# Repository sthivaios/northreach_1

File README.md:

# NorthReach 1

## Introduction

NorthReach 1 is a wired USB remote controller, to aid during presentations, particularly
on touchscreen interactive whiteboards.

Apart from basic features that other commercially available presenter remotes have, NorthReach
includes buttons for controlling Windows computers by default, such as a separate button for closing
the focused window, or a button to bring up Task Manager in the event that some application freezes.

The firmware is written in C, with the Espressif ESP-IDF framework. Through the `menuconfig` utility,
the board can be reconfigured to assign different actions to any button, for example to make the remote
compatible with MacOS.

Additionally, under the `hardware/` directory, the KiCad project for the PCB is available, as well
as the 3D printed enclosure inside `enclosure/`.

**The firmware and the PCB is only designed for ESP-S3 modules which natively support USB.**

In the future, there will also be a wireless version of NorthReach, possibly based on a Nordic nRF SoC.
However, for now, I'm focusing on the wired version.

## Contributing

You are more than welcome to contribute to the project, by forking then creating a pull request.
If you are an end user, feel free to request new features or report a bug by creating an issue
on this repository on GitHub.

If you are actually contributing code to the project, make sure that you understand the license terms.

## Licensing
This project contains multiple components under different licenses.
See [LICENSE](LICENSE) for more details.

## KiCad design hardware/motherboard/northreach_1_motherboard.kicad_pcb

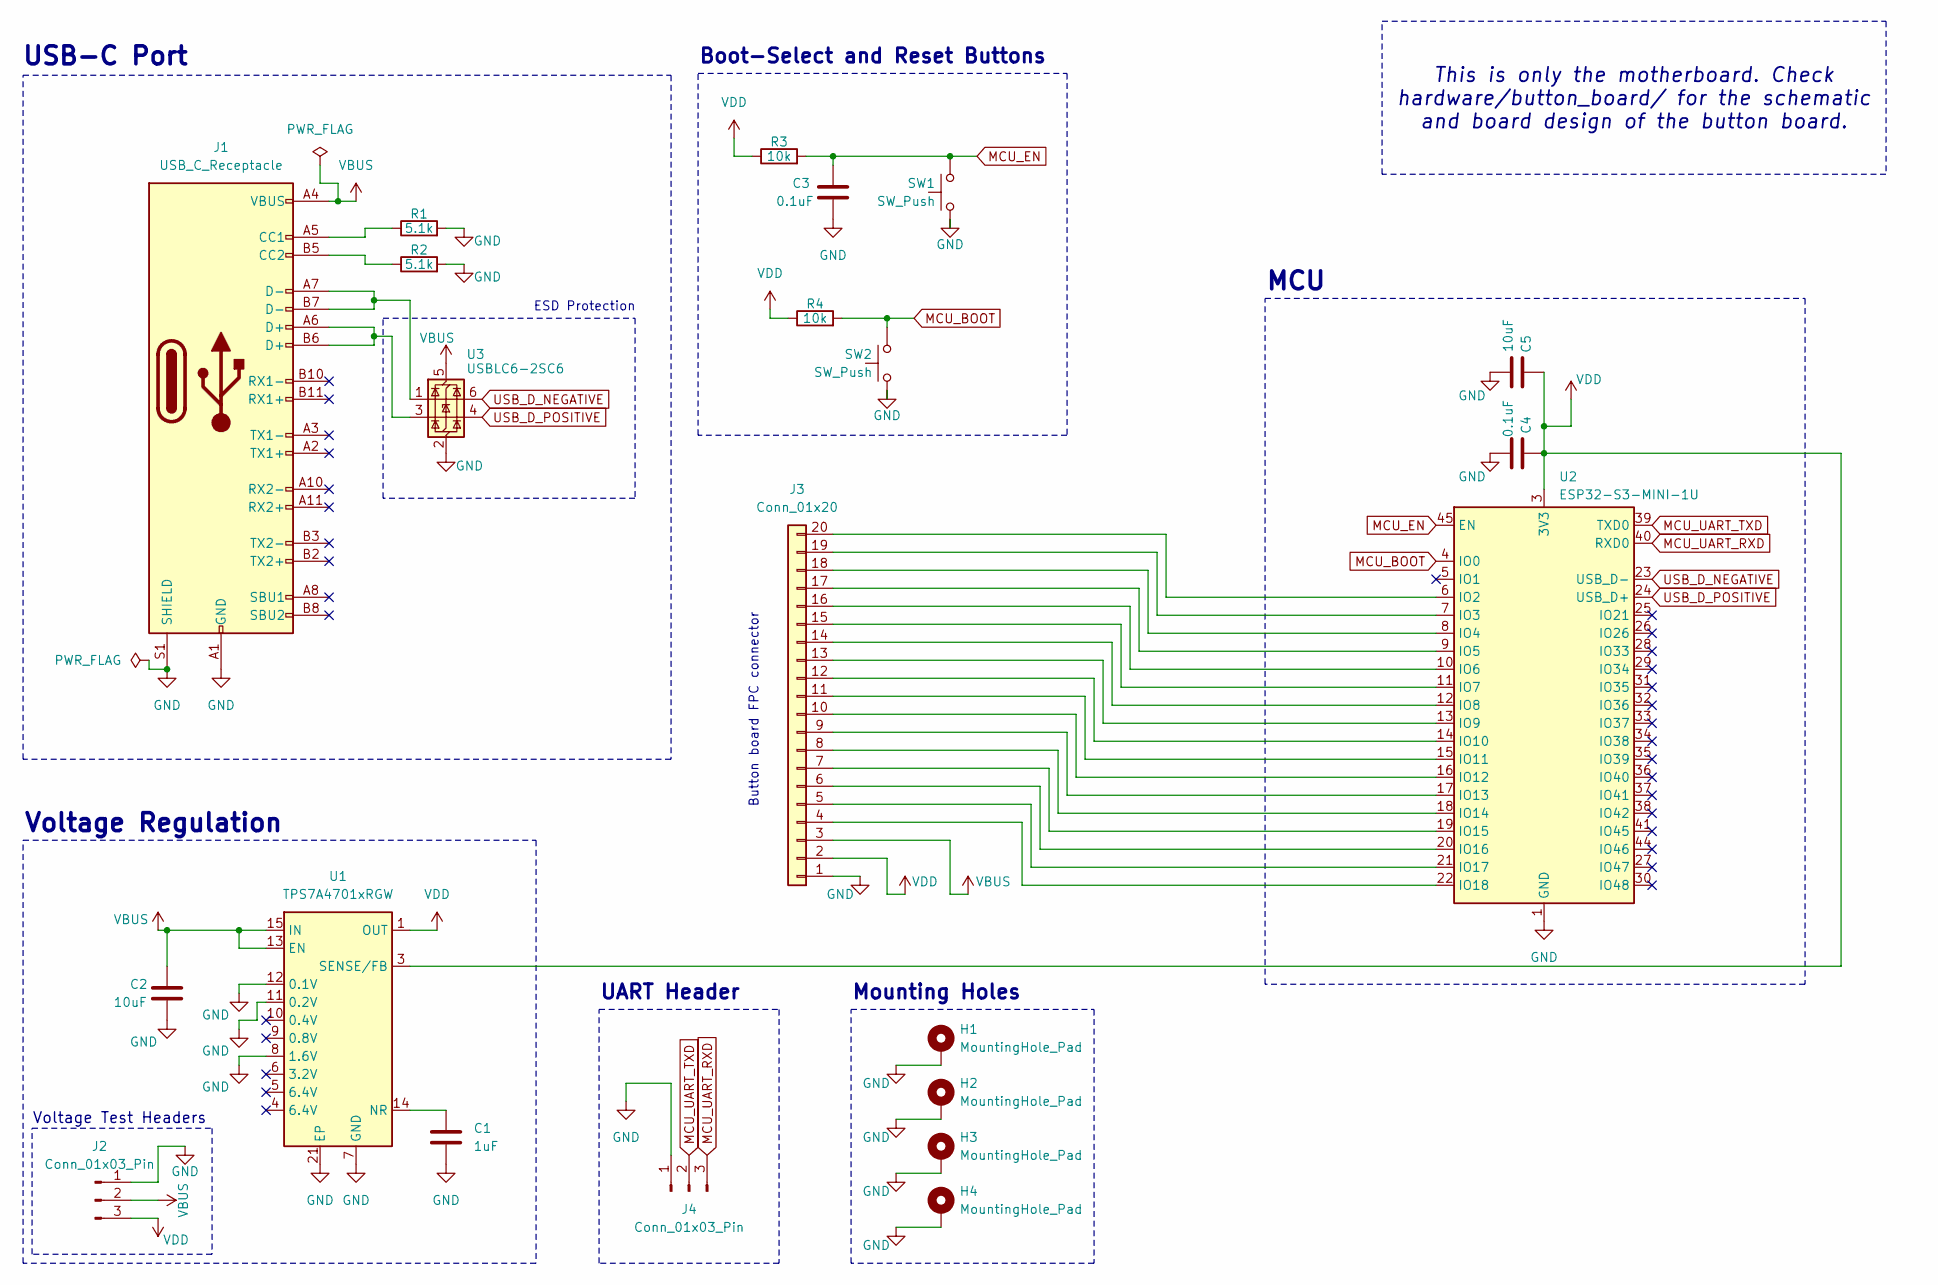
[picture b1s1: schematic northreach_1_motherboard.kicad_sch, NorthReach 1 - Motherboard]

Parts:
C1: 1uF; C_0805_2012Metric; LCSC C28323
C2, C5: 10uF; C_0805_2012Metric; LCSC C15850
C3, C4: 0.1uF; C_0805_2012Metric; LCSC C28233
H1, H2, H3, H4: MountingHole_Pad; MountingHole_2.2mm_M2_Pad
J1: USB_C_Receptacle; USB_C_Receptacle_Amphenol_12401610E4-2A; LCSC C5119948
J2, J4: Conn_01x03_Pin; PinHeader_1x03_P2.54mm_Vertical
J3: Conn_01x20; Hirose_FH12-20S-0.5SH_1x20-1MP_P0.50mm_Horizontal; LCSC C596730
R1, R2: 5.1k; R_0805_2012Metric; LCSC C84375
R3, R4: 10k; R_0805_2012Metric; LCSC C84376
SW1, SW2: SW_Push; SW_PUSH_6mm_H4.3mm
U1: TPS7A4701xRGW; Texas_RGW0020A_VQFN-20-1EP_5x5mm_P0.65mm_EP3.15x3.15mm_Ther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; LCSC C90084
U2: ESP32-S3-MINI-1U; ESP32-S2-MINI-1U; LCSC C2980299
U3: USBLC6-2SC6; SOT-23-6; LCSC C7519

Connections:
GND: C1.1, C2.1, C3.1, C4.1, C5.1, H1.1, H2.1, H3.1, H4.1, J1.A1 (GND), J1.A12 (GND), J1.B1 (GND), J1.B12 (GND), J1.S1 (SHIELD), J2.1, J3.1, J4.1, R1.2, R2.2, SW1.1, SW2.1, U1.7 (GND), U1.8 (1.6V), U1.11 (0.2V), U1.12 (0.1V), U1.21 (EP), U2.1 (GND), U2.2 (GND), U2.42 (GND), U2.43 (GND), U2.46 (GND), U2.47 (GND), U2.48 (GND), U2.49 (GND), U2.50 (GND), U2.51 (GND), U2.52 (GND), U2.53 (GND), U2.54 (GND), U2.55 (GND), U2.56 (GND), U2.57 (GND), U2.58 (GND), U2.59 (GND), U2.60 (GND), U2.61 (GND), U2.62 (GND), U2.63 (GND), U2.64 (GND), U2.65 (GND), U3.2 (GND)
MCU_BOOT: R4.2, SW2.2, U2.4 (IO0)
MCU_EN: C3.2, R3.2, SW1.2, U2.45 (EN)
MCU_UART_RXD: J4.3, U2.40 (RXD0)
MCU_UART_TXD: J4.2, U2.39 (TXD0)
unnamed: J1.A5 (CC1), R1.1
unnamed: J1.B5 (CC2), R2.1
unnamed: J1.A6 (D+), J1.B6 (D+), U3.3 (I/O2)
unnamed: J1.A7 (D-), J1.B7 (D-), U3.1 (I/O1)
unnamed: J3.4, U2.22 (IO18)
unnamed: J3.5, U2.21 (IO17)
unnamed: J3.6, U2.20 (IO16)
unnamed: J3.7, U2.19 (IO15)
unnamed: J3.8, U2.18 (IO14)
unnamed: J3.9, U2.17 (IO13)
unnamed: J3.10, U2.16 (IO12)
unnamed: J3.11, U2.15 (IO11)
unnamed: J3.12, U2.14 (IO10)
unnamed: J3.13, U2.13 (IO9)
unnamed: J3.14, U2.12 (IO8)
unnamed: J3.15, U2.11 (IO7)
unnamed: J3.16, U2.10 (IO6)
unnamed: J3.17, U2.9 (IO5)
unnamed: J3.18, U2.8 (IO4)
unnamed: J3.19, U2.7 (IO3)
unnamed: J3.20, U2.6 (IO2)
unnamed: C1.2, U1.14 (NR)
USB_D_NEGATIVE: U2.23 (USB_D-), U3.6 (I/O1)
USB_D_POSITIVE: U2.24 (USB_D+), U3.4 (I/O2)
VBUS: C2.2, J1.A4 (VBUS), J1.A9 (VBUS), J1.B4 (VBUS), J1.B9 (VBUS), J2.2, J3.3, U1.13 (EN), U1.15 (IN), U1.16 (IN), U3.5 (VBUS)
VDD: C4.2, C5.2, J2.3, J3.2, R3.1, R4.1, U1.1 (OUT), U1.3 (SENSE/FB), U1.20 (OUT), U2.3 (3V3)

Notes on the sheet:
Voltage Regulation
Voltage Test Headers
Mounting Holes
UART Header
Boot-Select and Reset Buttons
Button board FPC connector
MCU
ESD Protection
USB-C Port
This is only the motherboard. Check hardware/button_board/ for the schematic and board design of the button board.

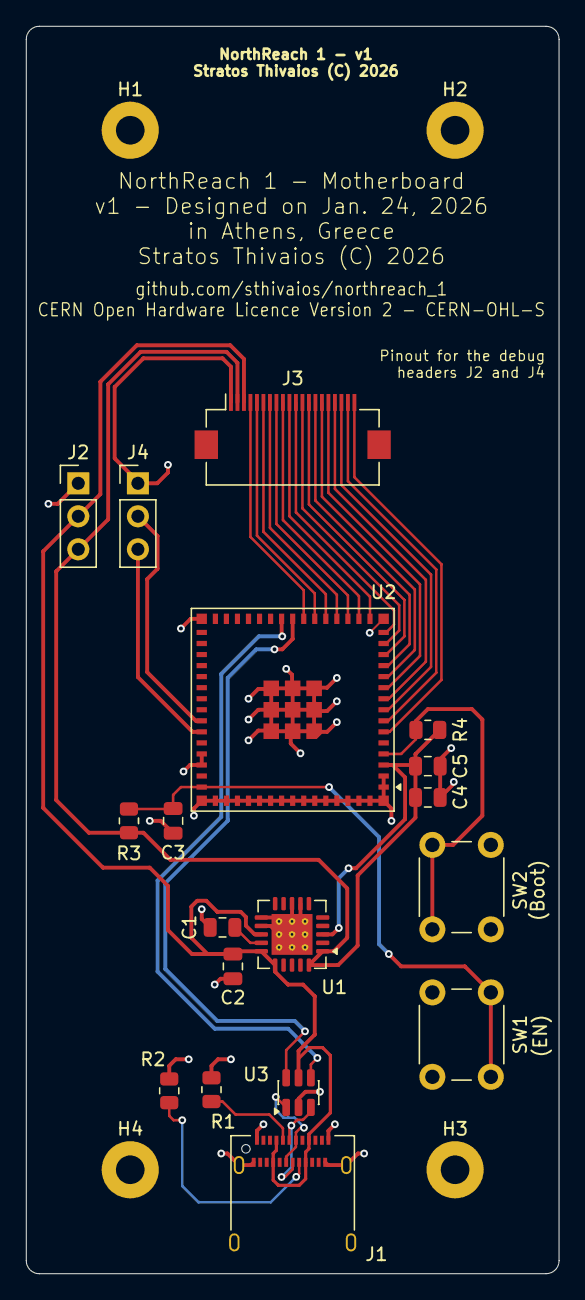
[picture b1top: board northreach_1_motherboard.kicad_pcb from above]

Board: 2 copper layers, 41.0 x 96.0 mm, 22 parts (0 on the bottom side), 31 nets.

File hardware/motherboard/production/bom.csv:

Designator,Footprint,Quantity,Value,LCSC Part #
C1,0805,1,1uF,C28323
"C2, C5",0805,2,10uF,C15850
"C3, C4",0805,2,0.1uF,C28233
J1,USB_C_Receptacle_Amphenol_12401610E4-2A,1,USB_C_Receptacle,C5119948
"J2, J4",PinHeader_1x03_P2.54mm_Vertical,2,Conn_01x03_Pin,
J3,Hirose_FH12-20S-0.5SH_1x20-1MP_P0.50mm_Horizontal,1,Conn_01x20,C596730
"R1, R2",0805,2,5.1k,C84375
"R3, R4",0805,2,10k,C84376
"SW1, SW2",SW_PUSH_6mm_H4.3mm,2,SW_Push,
U1,Texas_RGW0020A_VQFN-20-1EP_5x5mm_P0.65mm_EP3.15x3.15mm_ThermalVias,1,TPS7A4701xRGW,C90084
U2,ESP32-S2-MINI-1U,1,ESP32-S3-MINI-1U,C2980299
U3,SOT-23-6,1,USBLC6-2SC6,C7519

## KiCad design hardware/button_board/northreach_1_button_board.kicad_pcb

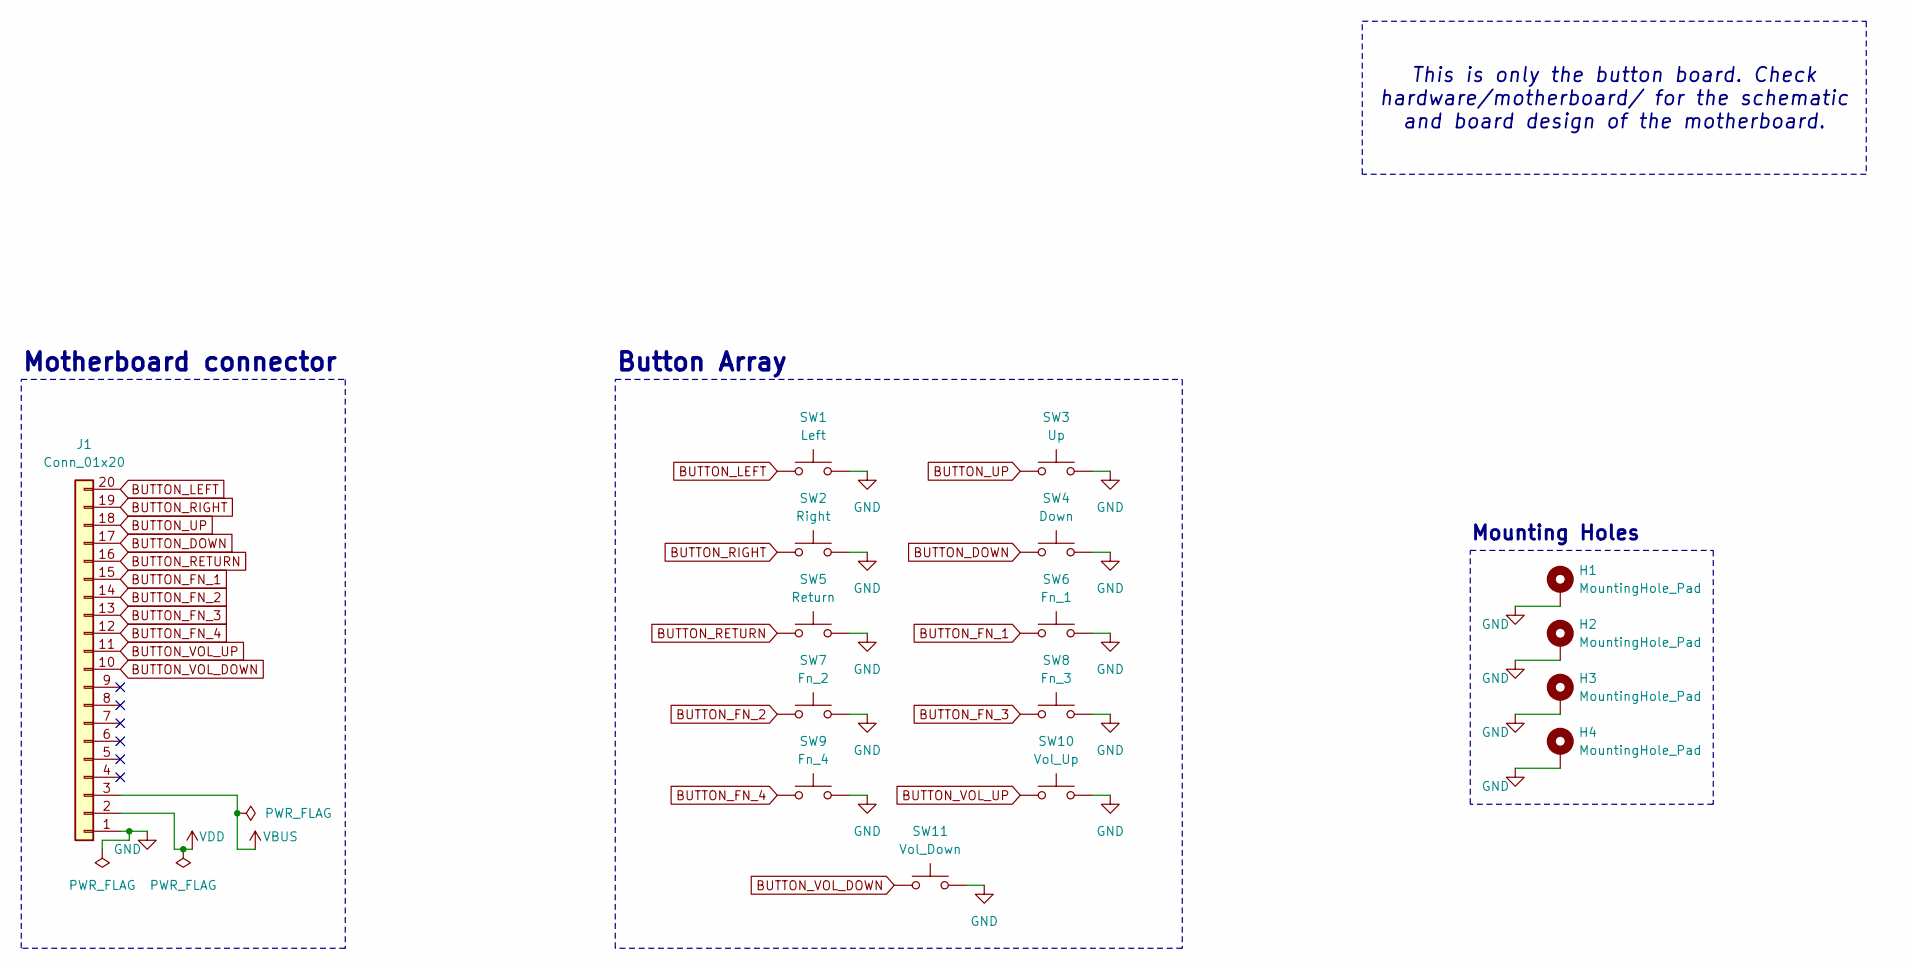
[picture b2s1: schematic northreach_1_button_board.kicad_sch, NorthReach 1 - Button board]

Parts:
H1, H2, H3, H4: MountingHole_Pad; MountingHole_2.2mm_M2_Pad
J1: Conn_01x20; Hirose_FH12-20S-0.5SH_1x20-1MP_P0.50mm_Horizontal; LCSC C596730
SW1: Left; SW_BUTTON_SoftTactile
SW2: Right; SW_BUTTON_SoftTactile
SW3: Up; SW_BUTTON_SoftTactile
SW4: Down; SW_BUTTON_SoftTactile
SW5: Return; SW_BUTTON_SoftTactile
SW6: Fn_1; SW_BUTTON_SoftTactile
SW7: Fn_2; SW_BUTTON_SoftTactile
SW8: Fn_3; SW_BUTTON_SoftTactile
SW9: Fn_4; SW_BUTTON_SoftTactile
SW10: Vol_Up; SW_BUTTON_SoftTactile
SW11: Vol_Down; SW_BUTTON_SoftTactile

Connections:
BUTTON_DOWN: J1.17, SW4.1
BUTTON_FN_1: J1.15, SW6.1
BUTTON_FN_2: J1.14, SW7.1
BUTTON_FN_3: J1.13, SW8.1
BUTTON_FN_4: J1.12, SW9.1
BUTTON_LEFT: J1.20, SW1.1
BUTTON_RETURN: J1.16, SW5.1
BUTTON_RIGHT: J1.19, SW2.1
BUTTON_UP: J1.18, SW3.1
BUTTON_VOL_DOWN: J1.10, SW11.1
BUTTON_VOL_UP: J1.11, SW10.1
GND: H1.1, H2.1, H3.1, H4.1, J1.1, SW1.2, SW2.2, SW3.2, SW4.2, SW5.2, SW6.2, SW7.2, SW8.2, SW9.2, SW10.2, SW11.2
VBUS: J1.3
VDD: J1.2

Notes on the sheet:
Motherboard connector
Mounting Holes
Button Array
This is only the button board. Check hardware/motherboard/ for the schematic and board design of the motherboard.

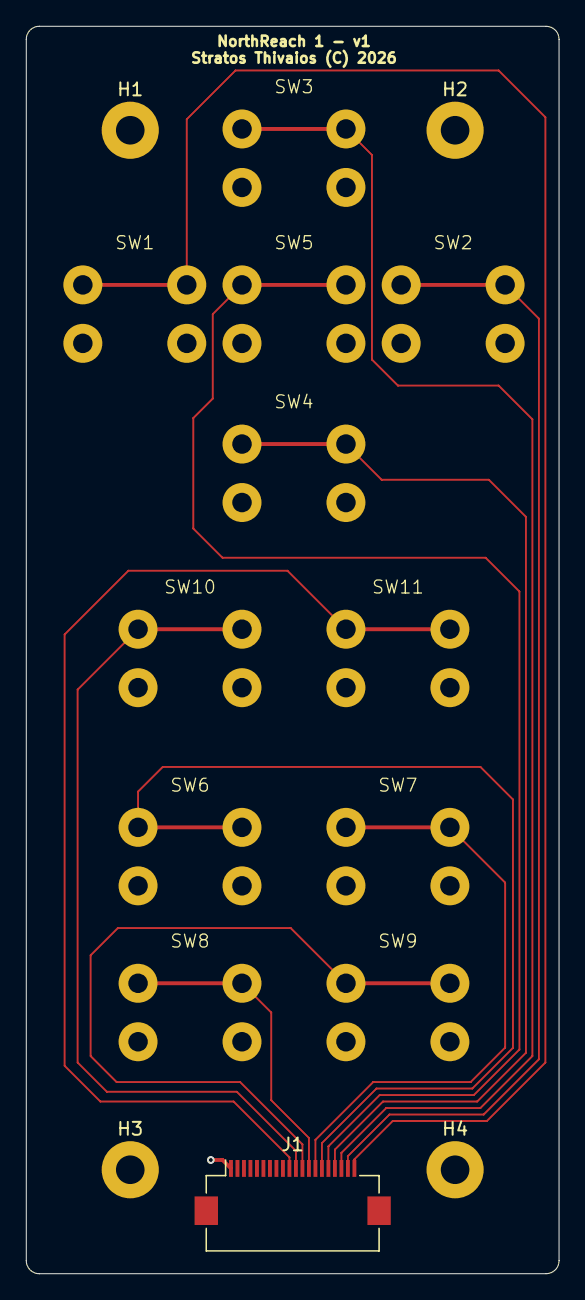
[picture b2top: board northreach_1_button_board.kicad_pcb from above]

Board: 2 copper layers, 41.0 x 96.0 mm, 16 parts (0 on the bottom side), 12 nets.

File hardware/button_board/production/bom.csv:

Designator,Footprint,Quantity,Value,LCSC Part #
J1,Hirose_FH12-20S-0.5SH_1x20-1MP_P0.50mm_Horizontal,1,Conn_01x20,
SW1,SW_BUTTON_SoftTactile,1,Left,
SW10,SW_BUTTON_SoftTactile,1,Vol_Up,
SW11,SW_BUTTON_SoftTactile,1,Vol_Down,
SW2,SW_BUTTON_SoftTactile,1,Right,
SW3,SW_BUTTON_SoftTactile,1,Up,
SW4,SW_BUTTON_SoftTactile,1,Down,
SW5,SW_BUTTON_SoftTactile,1,Return,
SW6,SW_BUTTON_SoftTactile,1,Fn_1,
SW7,SW_BUTTON_SoftTactile,1,Fn_2,
SW8,SW_BUTTON_SoftTactile,1,Fn_3,
SW9,SW_BUTTON_SoftTactile,1,Fn_4,

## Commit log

2026-01-05 add gitignore
2026-01-05 license and readme
2026-01-05 CERN-OHL-S license file in hardware/
2026-01-05 add kicad files
2026-01-06 schematic: usb-c port section
2026-01-06 kicad being annoying
2026-01-06 schematic: add voltage regulator
2026-01-06 enclosure: v1
2026-01-06 enclosure: stl exports of v1
2026-01-06 enclosure: v1 - update fillets and stuff
2026-01-06 enclosure: v2 - separate buttons
2026-01-06 schematic: add MCU, and bootselect and reset buttons
2026-01-06 schematic: MCU UART header
2026-01-06 schematic: reorganize it a little
2026-01-06 schematic: add button array and status led
2026-01-06 schematic: J4 was missing a footprint
2026-01-07 enclosure: clean new fusion project with components
2026-01-07 enclosure: v4: added standoffs
2026-01-07 git: update gitignore
2026-01-07 schematic: add M2 mounting holes (grounded)
2026-01-07 enclosure: add kicad reference sketch and export as dfx
2026-01-07 chore: separate schematics and stuff to two boards
2026-01-08 schematic: separate boards, add FPC connector
2026-01-08 schematic: update connector name lol
2026-01-08 pcb: button board: layout
2026-01-08 pcb: button board: routing
2026-01-08 pcb: button board: GND plane clearances
2026-01-08 pcb: button board: labels and copyright lol
2026-01-08 pcb: button board: add LCSC codes, generate production files
2026-01-08 schematic_and_pcb: button board: remove led for now
2026-01-08 pcb: button board: regenerate production files
2026-01-08 enclosure: minor changes, export new STLs
2026-01-09 chore: not entirely sure what the heck just changed but im committing it
2026-01-10 kicad: add LCSC parts
2026-01-10 chore: add esp-idf artifacts to gitignore
2026-01-10 esp-idf: start new project
2026-01-10 chore: licenses
2026-01-10 firmware: update some stuff
2026-01-11 firmware: add esp_tinyusb from esp component registry
2026-01-11 firmware: gitignore some stuff
2026-01-11 firmware: add sdkconfig to gitignore
2026-01-11 firmware: add hid.c to cmakelists.txt
2026-01-11 firmware: add hid.c and hid.h
2026-01-11 firmware: start the hid task in main.c
2026-01-14 firmware: add buttons.c and headers
2026-01-14 firmware: add buttons.c to CMakeLists.txt
2026-01-16 firmware: start button task in main.c
2026-01-16 firmware: deps: add the espressif/button component
2026-01-16 firmware: queue stuff in buttons.c
2026-01-16 firmware: receive from queue in hid.c
2026-01-16 firmware: remove unused header lol
2026-01-17 firmware: add espressif/button as a component dep
2026-01-17 firmware: init espressif/button with only one button for now
2026-01-17 firmware: register sample callback for button
2026-01-18 firmware: couple of buttons working
2026-01-19 firmware: remove BUTTON_SINGLE_CLICK event in favor of BUTTON_PRESS_DOWN for more responsive feel
2026-01-19 firmware: janky solution for a bug with macos that im trying to fix
2026-01-19 firmware: remove useless logs
2026-01-21 firmware: buttons.c: error handling, array-based button config, rename some stuff, add better logging
2026-01-21 firmware: buttons.h: update the values in the enum typedef to F1-f4
2026-01-21 firmware: hid.c remove disgusting switch for deciding which key to send
2026-01-21 firmware: reformat code lol
2026-01-21 firmware: consumer report protocol buttons (volume)
2026-01-21 firmware: consumer protocol working
2026-01-21 firmware: error handling
2026-01-21 firmware: keys with modifiers
2026-01-21 schematic: motherboard: change switch footprint for EN and RESET
2026-01-21 pcb: button board: place components
2026-01-21 pcb: motherboard: route stuff
2026-01-22 pcb: motherboard: silkscreen
2026-01-22 pcb: button board: silkscreen
2026-01-22 pcb: generate prod files
2026-01-23 schematic: motherboard: add usb esd protection
2026-01-23 pcb: motherboard: add ESD protection
2026-01-23 pcb: motherboard: fix silkscreen stuff
2026-01-23 schematic: motherboard: text, drawing sheet details
2026-01-23 schematic_and_pcb: button board: SW numbering
2026-01-23 pcb: motherboard: rev v2.0 generate prod files
2026-01-23 pcb: button_board: rev v1.1 generate prod files
2026-01-23 schematic_and_pcb: motherboard: route SENSE VREG pin to load
2026-01-23 schematic_and_pcb: motherboard: add ESD protection IC LCSC id
2026-01-23 pcb: motherboard: rev v2.1 generate prod files
2026-01-23 pcb: button_board: move J1 up
2026-01-23 pcb: button_board: rev v1.2 generate prod files
2026-01-23 pcb: button_board: move silkscreen, regenerate prod files
2026-01-23 pcb: motherboard: move silkscreen, regenerate prod files
2026-01-24 pcb: motherboard: proper footprint for buttons
2026-01-24 pcb: button_board: rev v1.3 generate prod files
2026-01-24 pcb: button_board: footprint pins were wrong for the SWs
2026-01-24 pcb: button_board: footprint pins were still wrong for the SWs lmao
2026-01-24 pcb: button_board: reroute buttons since the footprint was wrong
2026-01-24 pcb: button_board: rev v1.4 generate prod files
2026-01-27 pcb: button_board: change switch footprint pad size to 1.5mm/3mm
2026-01-27 pcb: button_board: use updated footprint
2026-01-27 pcb: button_board: rev v1.5 generate prod files
2026-01-28 enclosure: shorten button height
2026-02-01 enclosure: add single button STLs to exports
2026-02-01 pcb: button_board: rev 1.6: fix a trace
2026-02-01 pcb: button_board: rev1.6 generate production files

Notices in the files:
hardware/button_board/northreach_1_button_board.kicad_pcb:
CERN Open Hardware License v2 - Strongly Reciprocal
Copyright © 2026 Stratos Thivaios
Stratos Thivaios (C) 2026
CERN Open Hardware Licence Version 2 - CERN-OHL-S
